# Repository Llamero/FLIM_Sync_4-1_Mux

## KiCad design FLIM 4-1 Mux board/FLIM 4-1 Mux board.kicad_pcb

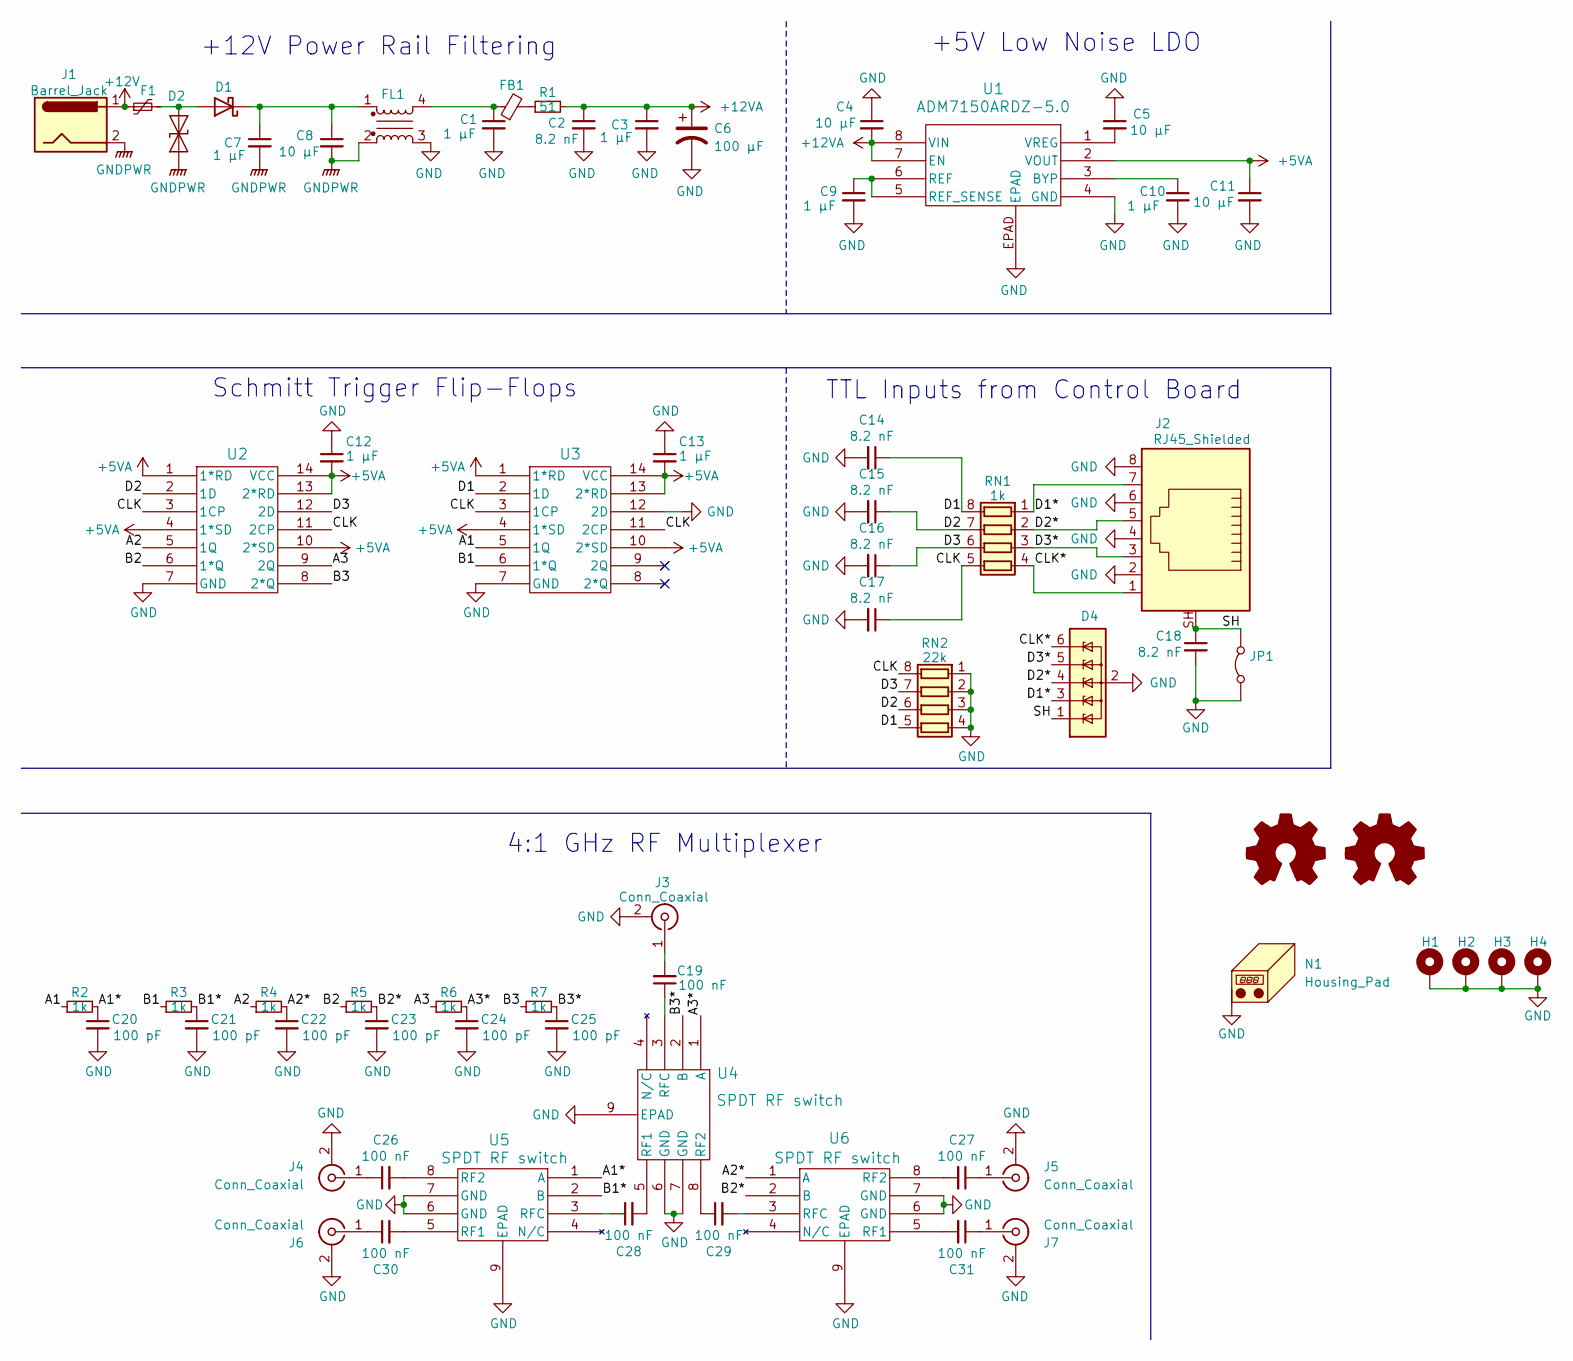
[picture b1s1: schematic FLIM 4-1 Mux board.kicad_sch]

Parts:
C1, C3, C7, C9, C10, C12, C13: 1 µF; C_0805_2012Metric; Part # 0805B105K500CT
C2, C14, C15, C16, C17, C18: 8.2 nF; C_0402_1005Metric; Part # GRM1555C1H822GE01D
C4, C5, C8, C11: 10 µF; C_1210_3225Metric; Part # 1210B106M500CT
C6: 100 µF; CP_Elec_10x10; Part # A768MS107M1JLAE027
C19, C26, C27, C28, C29, C30, C31: 100 nF; C_0201_0603Metric; Part # 0201BB104KW160
C20, C21, C22, C23, C24, C25: 100 pF; C_0402_1005Metric; Part # MT15N101J500CT
D1: D_Schottky; D_SOD-323; Part # NSR02100HT1G
D2: SMAJ13CA; D_SMA; Part # SMAJ13CA
D4: SMF05CT; SOT-363_SC-70-6; Part # SMF05CT
F1: Polyfuse_Small; Fuse_0603_1608Metric; Part # PRG18BC6R8MM1RB
FB1: FerriteBead_Small; L_0603_1608Metric; Part # MMZ1608B102CTD25
FL1: choke; WE-SL2; Part # 744222
H1, H2, H3, H4: MountingHole_4.3mm_M4_Pad_Via; Part # M2165-4007-AL-7
J1: Barrel_Jack; CONN4_00165_TEN; Part # 54-00165
J2: RJ45_Shielded; AMPHENOL_RJE3A1886102N; Part # RJE3A1886102N
J3, J4, J5, J6, J7: Conn_Coaxial; 60312242114510; Part # 60312242114510
JP1: Jumper_2_Bridged; SolderJumper-2_P1.3mm_Bridged_RoundedPad1.0x1.5mm
N1: Housing_Pad; Part # AU-1028
R1: 51; R_0805_2012Metric; Part # TNPW080551R0BEEA
R2, R3, R4, R5, R6, R7: 1k; R_0402_1005Metric; Part # RNCP0402FTD1K00
RN1: 1k; R_Array_Convex_4x0603; Part # CAY16-1001F4LF
RN2: 22k; R_Array_Convex_4x0603; Part # CAY16-2202F4LF
SYM1: Logo_Open_Hardware_Small; OSHW-Logo_5.7x6mm_SilkScreen
SYM2: Logo_Open_Hardware_Small; CC-BY-SA Symbol
U1: ADM7150ARDZ-5.0; ADM7150ARDZ-5; Part # ADM7150ARDZ-5.0
U2, U3: 74AHCT74D_118; 74AHCT74D_118_NEX; Part # 74AHCT74D,118
U4, U5, U6: SPDT RF switch; MSOP8G_8_ADI; Part # HMC284AMS8GETR

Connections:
+5VA: C11.1, C12.2, C13.2, U1.2 (VOUT), U2.1 (1*RD), U2.4 (1*SD), U2.10 (2*SD), U2.13 (2*RD), U2.14 (VCC), U3.1 (1*RD), U3.4 (1*SD), U3.10 (2*SD), U3.13 (2*RD), U3.14 (VCC)
+12V: F1.1, J1.1
+12VA: C2.1, C3.1, C4.2, C6.1, R1.2, U1.7 (EN), U1.8 (VIN)
/A1: R2.1, U3.5 (1Q)
/A1*: C20.1, R2.2, U5.1 (A)
/A2: R4.1, U2.5 (1Q)
/A2*: C22.1, R4.2, U6.1 (A)
/A3: R6.1, U2.9 (2Q)
/A3*: C24.1, R6.2, U4.1 (A)
/B1: R3.1, U3.6 (1*Q)
/B1*: C21.1, R3.2, U5.2 (B)
/B2: R5.1, U2.6 (1*Q)
/B2*: C23.1, R5.2, U6.2 (B)
/B3: R7.1, U2.8 (2*Q)
/B3*: C25.1, R7.2, U4.2 (B)
/CLK: C17.1, RN1.5 (R4.2), RN2.8 (R1.2), U2.3 (1CP), U2.11 (2CP), U3.3 (1CP), U3.11 (2CP)
/CLK*: D4.6 (IO5), J2.1, RN1.4 (R4.1)
/D1: C14.1, RN1.8 (R1.2), RN2.5 (R4.2), U3.2 (1D)
/D1*: D4.3 (IO2), J2.7, RN1.1 (R1.1)
/D2: C15.1, RN1.7 (R2.2), RN2.6 (R3.2), U2.2 (1D)
/D2*: D4.4 (IO3), J2.5, RN1.2 (R2.1)
/D3: C16.1, RN1.6 (R3.2), RN2.7 (R2.2), U2.12 (2D)
/D3*: D4.5 (IO4), J2.3, RN1.3 (R3.1)
/SH: C18.1, D4.1 (IO1), J2.SH, JP1.2 (B)
GND: C1.2, C2.2, C3.2, C4.1, C5.1, C6.2, C9.2, C10.2, C11.2, C12.1, C13.1, C14.2, C15.2, C16.2, C17.2, C18.2, C20.2, C21.2, C22.2, C23.2, C24.2, C25.2, D4.2 (GND), FL1.3, H1.1 (1_1), H2.1 (1_1), H3.1 (1_1), H4.1 (1_1), J2.2, J2.4, J2.6, J2.8, J3.2 (Ext), J4.2 (Ext), J5.2 (Ext), J6.2 (Ext), J7.2 (Ext), JP1.1 (A), N1.1, RN2.1 (R1.1), RN2.2 (R2.1), RN2.3 (R3.1), RN2.4 (R4.1), U1.4 (GND), U1.EPAD, U2.7 (GND), U3.7 (GND), U3.12 (2D), U4.6 (GND), U4.7 (GND), U4.9 (EPAD), U5.6 (GND), U5.7 (GND), U5.9 (EPAD), U6.6 (GND), U6.7 (GND), U6.9 (EPAD)
GNDPWR: C7.2, C8.2, D2.2 (A2), FL1.2, J1.2
unnamed: C1.1, FB1.1, FL1.4
unnamed: D1.2 (A), D2.1 (A1), F1.2
unnamed: C7.1, C8.1, D1.1 (K), FL1.1
unnamed: FB1.2, R1.1
unnamed: C19.2, J3.1 (In)
unnamed: C26.1, J4.1 (In)
unnamed: C27.1, J5.1 (In)
unnamed: C30.1, J6.1 (In)
unnamed: C31.1, J7.1 (In)
unnamed: C10.1, U1.3 (BYP)
unnamed: C9.1, U1.5 (REF_SENSE), U1.6 (REF)
unnamed: C5.2, U1.1 (VREG)
unnamed: C28.2, U4.5 (RF1)
unnamed: C29.1, U4.8 (RF2)
unnamed: C19.1, U4.3 (RFC)
unnamed: C30.2, U5.5 (RF1)
unnamed: C26.2, U5.8 (RF2)
unnamed: C28.1, U5.3 (RFC)
unnamed: C31.2, U6.5 (RF1)
unnamed: C27.2, U6.8 (RF2)
unnamed: C29.2, U6.3 (RFC)

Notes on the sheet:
+12V Power Rail Filtering
Schmitt Trigger Flip-Flops
+5V Low Noise LDO
TTL Inputs from Control Board
4:1 GHz RF Multiplexer

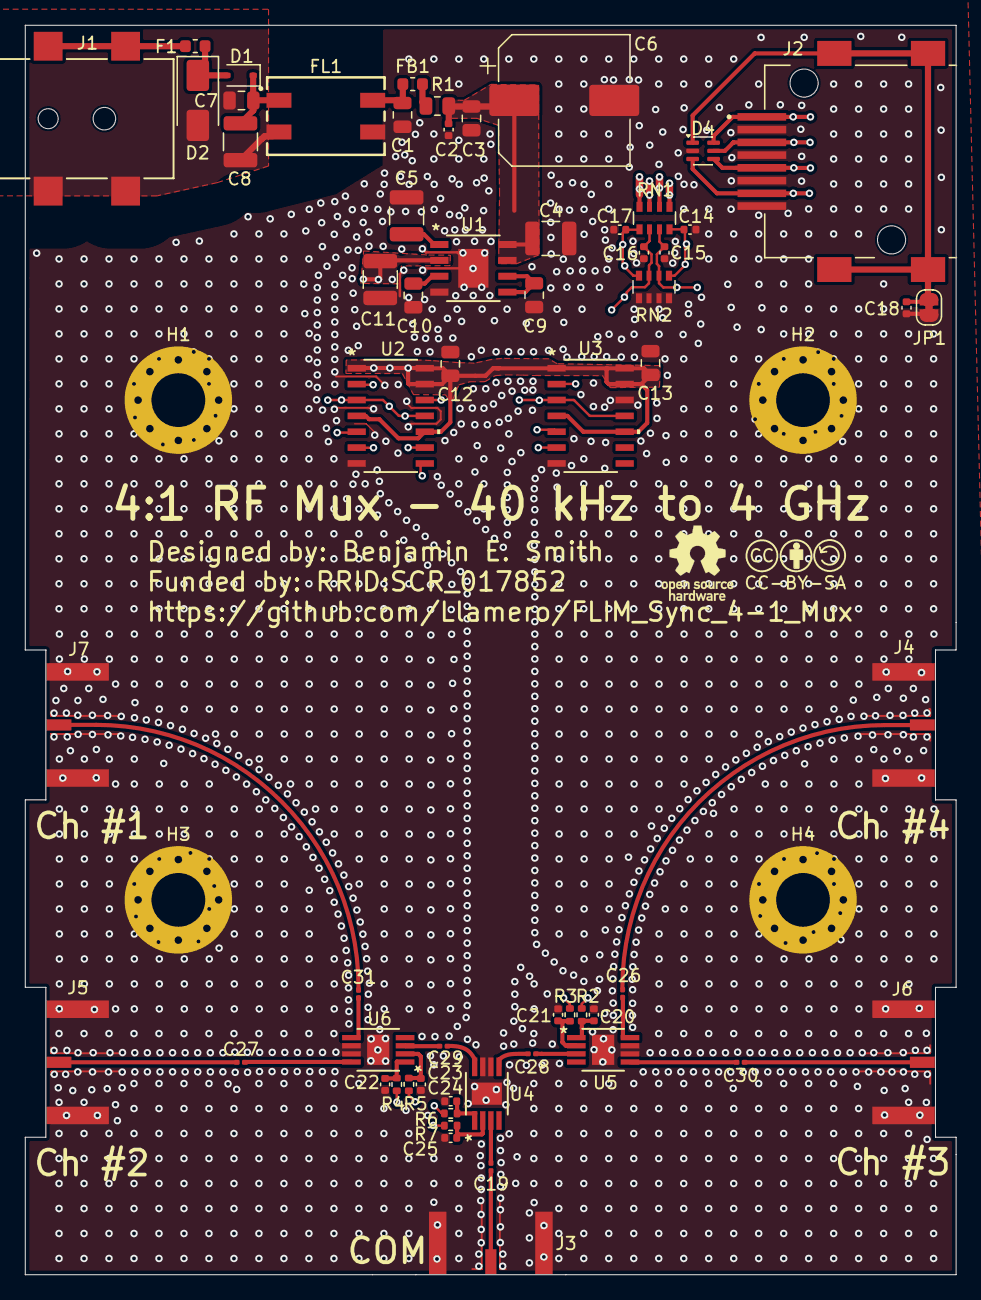
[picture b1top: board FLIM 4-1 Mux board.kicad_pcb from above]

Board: 4 copper layers, 74.5 x 100.0 mm, 66 parts (0 on the bottom side), 47 nets.
